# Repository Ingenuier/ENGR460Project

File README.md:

# ENGR460Project
Early design of a arduino controlled solar charger for cell phones

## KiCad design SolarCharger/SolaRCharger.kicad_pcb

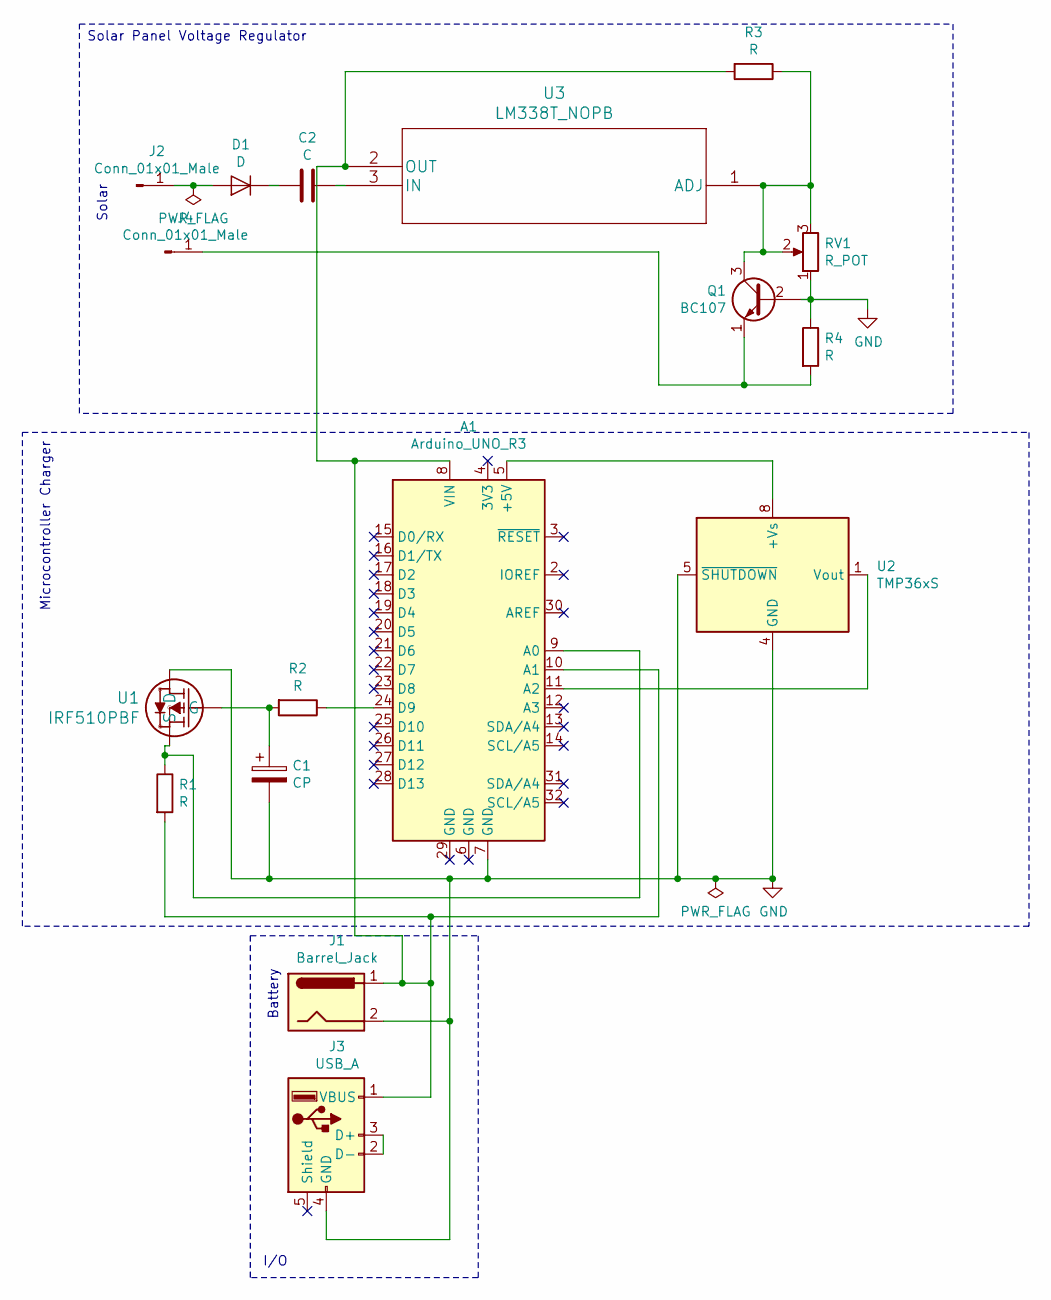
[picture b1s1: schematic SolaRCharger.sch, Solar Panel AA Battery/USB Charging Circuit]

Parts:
A1: Arduino_UNO_R3
C1: CP; CP_Elec_3x5.3
C2: C; C_0805_2012Metric
D1: D; D_0805_2012Metric
J1: Barrel_Jack; BarrelJack_CUI_PJ-063AH_Horizontal
J2, J4: Conn_01x01_Male; PinHeader_1x01_P2.54mm_Horizontal
J3: USB_A; USB3_A_Plug_Wuerth_692112030100_Horizontal
Q1: BC107; TO-18-3
R1, R2, R3, R4: R; R_0805_2012Metric
RV1: R_POT; Potentiometer_ACP_CA6-VSMD_Vertical
U1: IRF510PBF
U2: TMP36xS; SOIC-8_3.9x4.9mm_P1.27mm
U3: LM338T_NOPB; LM338T&slash_NOPB

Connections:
GND: A1.7 (GND), C1.2, J1.2, J3.4 (GND), Q1.2 (B), R4.1, RV1.1, U1.2 (D), U2.4 (GND), U2.5 (~SHUTDOWN)
unnamed: A1.5 (+5V), U2.8 (+Vs)
unnamed: A1.9 (A0), R1.1, U1.3 (S)
unnamed: A1.8 (VIN), A1.10 (A1), J1.1, J3.1 (VBUS), R1.2, R3.2, U3.2 (OUT)
unnamed: A1.11 (A2), U2.1 (Vout)
unnamed: A1.24 (D9), R2.1
unnamed: C1.1, R2.2, U1.1 (G)
unnamed: C2.1, D1.1 (K)
unnamed: C2.2, U3.3 (IN)
unnamed: D1.2 (A), J2.1
unnamed: J3.2 (D-), J3.3 (D+)
unnamed: J4.1, Q1.1 (E), R4.2
unnamed: Q1.3 (C), R3.1, RV1.2, RV1.3, U3.1 (ADJ)

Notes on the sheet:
Microcontroller Charger
Solar Panel Voltage Regulator
I/O
Battery
Solar

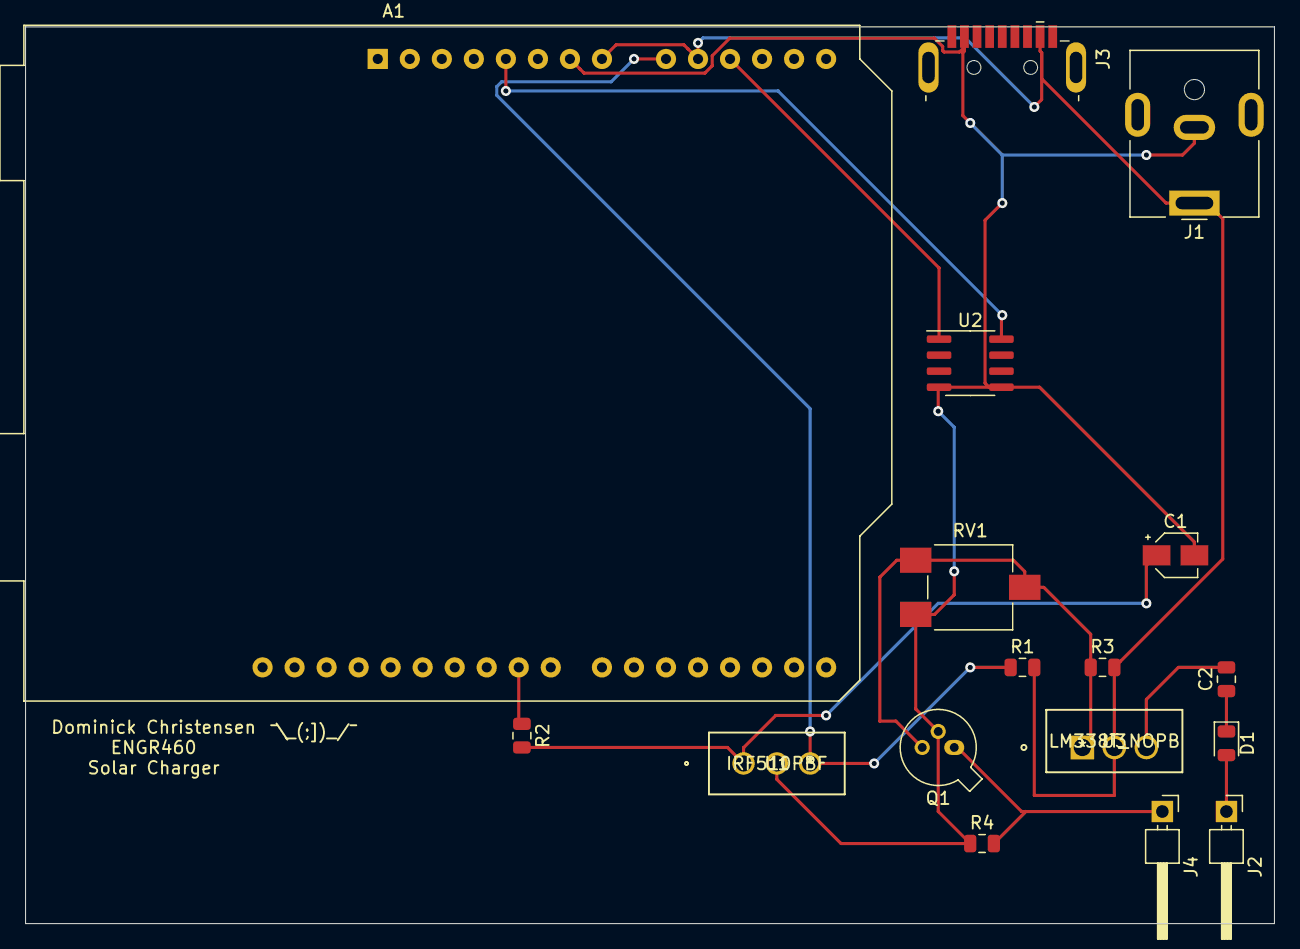
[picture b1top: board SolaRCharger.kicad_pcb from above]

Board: 2 copper layers, 99.1 x 71.1 mm, 17 parts (0 on the bottom side), 13 nets.

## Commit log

2020-06-11 added some images
2020-06-11 added more images, and bom
2020-06-11 bom again
2020-06-11 more image
2020-06-11 added some files, reorganized everything into folders, etc.

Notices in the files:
parts and their libraries:
Copyright 2016 Accelerated Designs. All rights reserved.
